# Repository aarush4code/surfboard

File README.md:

# surfboard

This is a devboard made with rp2040. It has 40 pins and 3 LEDs.

While making the devboard, or surfboard, I learned more about creating things in the kicad shematic, and how to route wires when their is a tight space. I also learned how to add labels to wire components together in the schematic.

## Images

## Bill of Materials
| Item                | Unit Price ($) | Link                                                                 | Quantity | Total ($) |
|---------------------|----------------|----------------------------------------------------------------------|----------|-----------|
| Capacitor 0.1uF     | 0.30           | [C52923](https://www.lcsc.com/product-detail/C52923.html?s_z=n_CL05A105KA5NQNC) | 11       | 3.30      |
| Capacitor 33pF      | 0.10           | [C1562](https://www.lcsc.com/product-detail/C1562.html?s_z=n_0402CG330J500NT)   | 2        | 0.20      |
| Capacitor 1uF       | 0.25           | [C42431804](https://www.lcsc.com/product-detail/C42431804.html)                 | 2        | 0.50      |
| Capacitor 10uF      | 0.29           | [C19702](https://www.lcsc.com/product-detail/C19702.html?s_z=n_CL10A106KP8NNNC) | 2        | 0.58      |
| Resistor 27Ω        | 0.60           | [C25100](https://www.lcsc.com/product-detail/C25100.html)                       | 2        | 1.20      |
| Resistor 1KΩ        | 0.06           | [C11702](https://www.lcsc.com/product-detail/C11702.html?s_z=n_0402WGF1001TCE)  | 2        | 0.12      |
| Resistor 5.1KΩ      | 0.05           | [C25905](https://www.lcsc.com/product-detail/C25905.html?s_z=n_0402WGF5101TCE)  | 2        | 0.10      |
| Resistor 10KΩ       | 0.06           | [C25744](https://www.lcsc.com/product-detail/C25744.html?s_z=n_0402WGF1002TCE)  | 1        | 0.06      |
| SK6812MINI LED      | 0.43           | [C5149201](https://www.lcsc.com/product-detail/C5149201.html)                   | 3        | 1.29      |
| 1x03 Pin Header     | 0.00           | [C42431804](https://www.lcsc.com/product-detail/C42431804.html)                 | 1        | 0.00      |
| 1x20 Pin Header     | 0.17           | [C42431804](https://www.lcsc.com/product-detail/C42431804.html)                 | 2        | 0.34      |
| 12 MHz Crystal      | 0.67           | [C9002](https://www.lcsc.com/product-detail/C9002.html?s_z=n_X322512MSB4SI)     | 1        | 0.67      |
| USB-C Receptacle    | 0.88           | [C165948](https://www.lcsc.com/product-detail/C165948.html?s_z=n_TYPE-C-31-M-12)| 1        | 0.88      |
| Flash Memory        | 0.95           | [C179171](https://www.lcsc.com/product-detail/C179171.html?s_z=n_Winbond%2520W25Q128JVSs)    | 1        | 1.60      |
| Voltage Regulator   | 0.33           | [C3054](https://www.lcsc.com/product-detail/C3054.html?s_z=n_IRFL9014TRPBF)     | 1        | 1.36      |
| Button              | 0.42           | [C2891841](https://www.lcsc.com/product-detail/C2891841.html)                     | 1        | 0.42      |
| RP2040              | 0.95           | [C2040](https://www.lcsc.com/product-detail/C2040.html?s_z=n_RP2040)            | 1        | 0.95      |
| PCBA                | 44.02          | [JLCPCB](https://jlcpcb.com)                                                    | 1        | 44.02     |
| **Total**           | --            | —                                                                                | —        | **57.89** |

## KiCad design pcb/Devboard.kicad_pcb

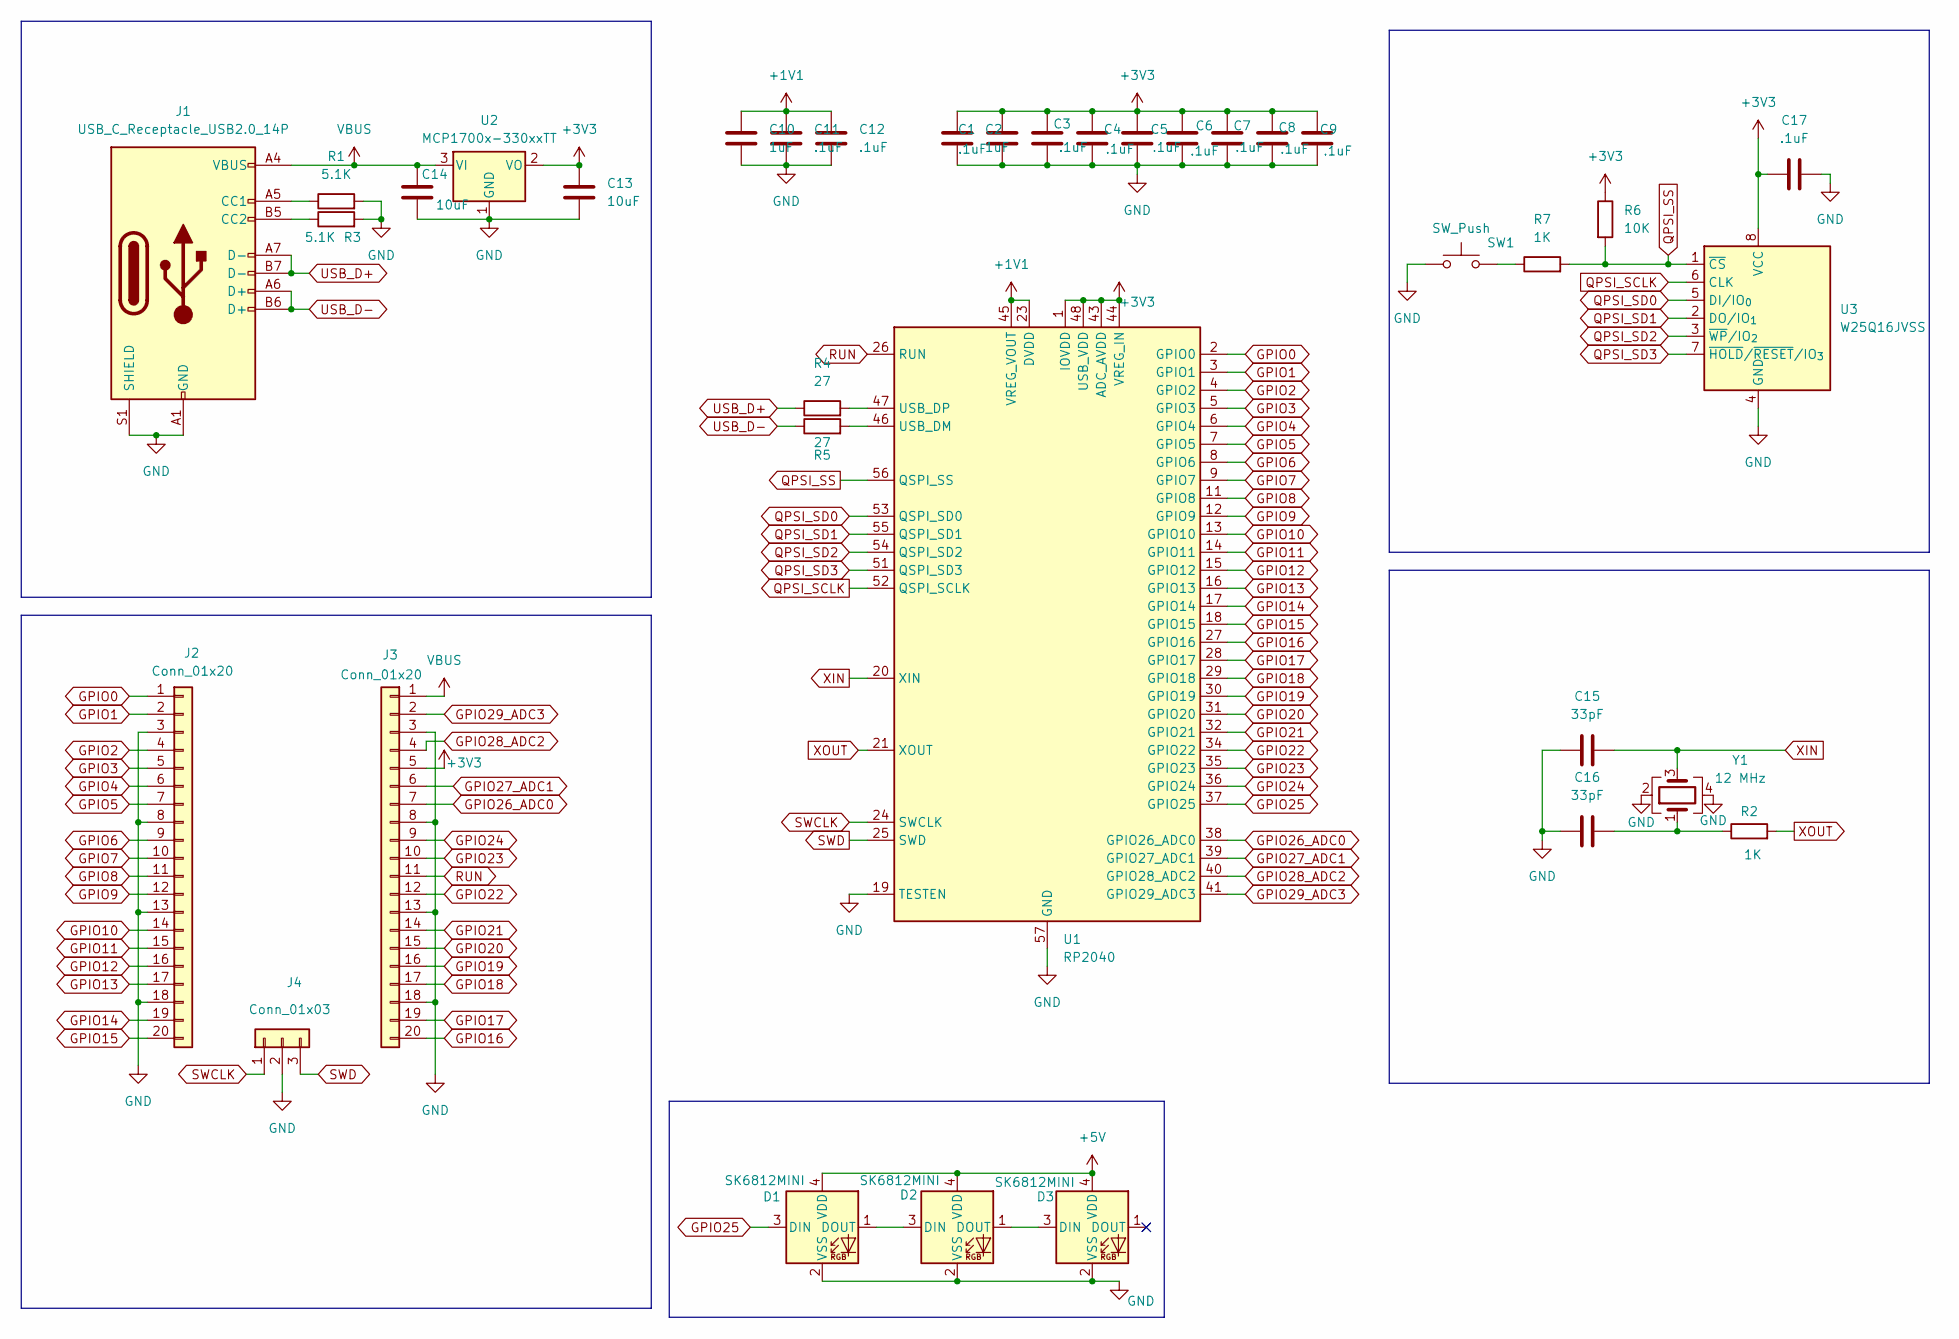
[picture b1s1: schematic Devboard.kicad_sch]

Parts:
C1, C3, C4, C5, C6, C7, C8, C9, C11, C12, C17: .1uF; C_0402_1005Metric
C2, C10: 1uF; C_0402_1005Metric
C13, C14: 10uF; C_0402_1005Metric
C15, C16: 33pF; C_0402_1005Metric
D1, D2, D3: SK6812MINI; LED_SK6812MINI_PLCC4_3.5x3.5mm_P1.75mm
J1: USB_C_Receptacle_USB2.0_14P; USB_C_Receptacle_HRO_TYPE-C-31-M-12
J2, J3: Conn_01x20; PinHeader_1x20_P2.54mm_Vertical
J4: Conn_01x03; PinHeader_1x03_P2.54mm_Vertical
R1, R3: 5.1K; R_0402_1005Metric
R2, R7: 1K; R_0402_1005Metric
R4, R5: 27; R_0402_1005Metric
R6: 10K; R_0402_1005Metric
SW1: SW_Push; SW_Push_SPST_NO_Alps_SKRK
U1: RP2040; QFN-56-1EP_7x7mm_P0.4mm_EP3.2x3.2mm
U2: MCP1700x-330xxTT; SOT-23
U3: W25Q16JVSS; Winbond_USON-8-1EP_3x2mm_P0.5mm_EP0.2x1.6mm
Y1: 12 MHz; Crystal_SMD_3225-4Pin_3.2x2.5mm

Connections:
+1V1: C10.1, C11.1, C12.1, U1.23 (DVDD), U1.45 (VREG_VOUT), U1.50 (DVDD)
+3V3: C1.1, C2.1, C3.1, C4.1, C5.1, C6.1, C7.1, C8.1, C9.1, C13.1, C17.1, J3.5, R6.1, U1.1 (IOVDD), U1.10 (IOVDD), U1.22 (IOVDD), U1.33 (IOVDD), U1.42 (IOVDD), U1.43 (ADC_AVDD), U1.44 (VREG_IN), U1.48 (USB_VDD), U1.49 (IOVDD), U2.2 (VO), U3.8 (VCC)
+5V: D1.4 (VDD), D2.4 (VDD), D3.4 (VDD)
GND: C1.2, C2.2, C3.2, C4.2, C5.2, C6.2, C7.2, C8.2, C9.2, C10.2, C11.2, C12.2, C13.2, C14.2, C15.1, C16.1, C17.2, D1.2 (VSS), D2.2 (VSS), D3.2 (VSS), J1.A1 (GND), J1.A12 (GND), J1.B1 (GND), J1.B12 (GND), J1.S1 (SHIELD), J2.3, J2.8, J2.13, J2.18, J3.3, J3.8, J3.13, J3.18, J4.2, R1.2, R3.2, SW1.1, U1.19 (TESTEN), U1.57 (GND), U2.1 (GND), U3.4 (GND), Y1.2, Y1.4
GPIO0: J2.1, U1.2 (GPIO0)
GPIO1: J2.2, U1.3 (GPIO1)
GPIO2: J2.4, U1.4 (GPIO2)
GPIO3: J2.5, U1.5 (GPIO3)
GPIO4: J2.6, U1.6 (GPIO4)
GPIO5: J2.7, U1.7 (GPIO5)
GPIO6: J2.9, U1.8 (GPIO6)
GPIO7: J2.10, U1.9 (GPIO7)
GPIO8: J2.11, U1.11 (GPIO8)
GPIO9: J2.12, U1.12 (GPIO9)
GPIO10: J2.14, U1.13 (GPIO10)
GPIO11: J2.15, U1.14 (GPIO11)
GPIO12: J2.16, U1.15 (GPIO12)
GPIO13: J2.17, U1.16 (GPIO13)
GPIO14: J2.19, U1.17 (GPIO14)
GPIO15: J2.20, U1.18 (GPIO15)
GPIO16: J3.20, U1.27 (GPIO16)
GPIO17: J3.19, U1.28 (GPIO17)
GPIO18: J3.17, U1.29 (GPIO18)
GPIO19: J3.16, U1.30 (GPIO19)
GPIO20: J3.15, U1.31 (GPIO20)
GPIO21: J3.14, U1.32 (GPIO21)
GPIO22: J3.12, U1.34 (GPIO22)
GPIO23: J3.10, U1.35 (GPIO23)
GPIO24: J3.9, U1.36 (GPIO24)
GPIO25: D1.3 (DIN), U1.37 (GPIO25)
GPIO26_ADC0: J3.7, U1.38 (GPIO26_ADC0)
GPIO27_ADC1: J3.6, U1.39 (GPIO27_ADC1)
GPIO28_ADC2: J3.4, U1.40 (GPIO28_ADC2)
GPIO29_ADC3: J3.2, U1.41 (GPIO29_ADC3)
unnamed: C16.2, R2.1, Y1.1
unnamed: D1.1 (DOUT), D2.3 (DIN)
unnamed: D2.1 (DOUT), D3.3 (DIN)
unnamed: J1.A5 (CC1), R1.1
unnamed: J1.B5 (CC2), R3.1
unnamed: R7.1, SW1.2
unnamed: R5.2, U1.46 (USB_DM)
unnamed: R4.2, U1.47 (USB_DP)
QPSI_SCLK: U1.52 (QSPI_SCLK), U3.6 (CLK)
QPSI_SD0: U1.53 (QSPI_SD0), U3.5 (DI/IO_{0})
QPSI_SD1: U1.55 (QSPI_SD1), U3.2 (DO/IO_{1})
QPSI_SD2: U1.54 (QSPI_SD2), U3.3 (~WP/IO_{2})
QPSI_SD3: U1.51 (QSPI_SD3), U3.7 (~HOLD/~RESET/IO_{3})
QPSI_SS: R6.2, R7.2, U1.56 (QSPI_SS), U3.1 (~CS)
RUN: J3.11, U1.26 (RUN)
SWCLK: J4.1, U1.24 (SWCLK)
SWD: J4.3, U1.25 (SWD)
USB_D+: J1.A7 (D-), J1.B7 (D-), R4.1
USB_D-: J1.A6 (D+), J1.B6 (D+), R5.1
VBUS: C14.1, J1.A4 (VBUS), J1.A9 (VBUS), J1.B4 (VBUS), J1.B9 (VBUS), J3.1, U2.3 (VI)
XIN: C15.2, U1.20 (XIN), Y1.3
XOUT: R2.2, U1.21 (XOUT)

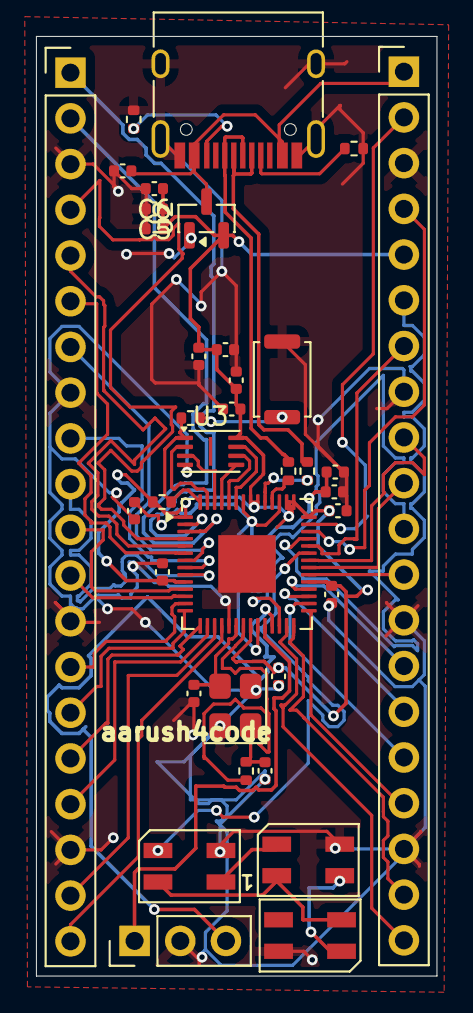
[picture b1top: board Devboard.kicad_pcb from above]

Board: 2 copper layers, 22.2 x 52.2 mm, 36 parts (0 on the bottom side), 56 nets.

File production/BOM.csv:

"Id";"Designator";"Footprint";"Quantity";"Designation";"Supplier and ref";
1;"C11,C12,C17,C8,C3,C9,C4,C1,C7,C6,C5";"C_0402_1005Metric";11;".1uF";;;
2;"C2,C10";"C_0402_1005Metric";2;"1uF";;;
3;"U3";"Winbond_USON-8-1EP_3x2mm_P0.5mm_EP0.2x1.6mm";1;"W25Q16JVSS";;;
4;"U2";"SOT-23";1;"MCP1700x-330xxTT";;;
5;"C16,C15";"C_0402_1005Metric";2;"33pF";;;
6;"J1";"USB_C_Receptacle_HRO_TYPE-C-31-M-12";1;"USB_C_Receptacle_USB2.0_14P";;;
7;"J3,J2";"PinHeader_1x20_P2.54mm_Vertical";2;"Conn_01x20";;;
8;"R2,R7";"R_0402_1005Metric";2;"1K";;;
9;"C14,C13";"C_0402_1005Metric";2;"10uF";;;
10;"D1,D2,D3";"LED_SK6812MINI_PLCC4_3.5x3.5mm_P1.75mm";3;"SK6812MINI";;;
11;"R5,R4";"R_0402_1005Metric";2;"27";;;
12;"J4";"PinHeader_1x03_P2.54mm_Vertical";1;"Conn_01x03";;;
13;"Y1";"Crystal_SMD_3225-4Pin_3.2x2.5mm";1;"12 MHz";;;
14;"R3,R1";"R_0402_1005Metric";2;"5.1K";;;
15;"SW1";"SW_Push_SPST_NO_Alps_SKRK";1;"SW_Push";;;
16;"U1";"QFN-56-1EP_7x7mm_P0.4mm_EP3.2x3.2mm";1;"RP2040";;;
17;"R6";"R_0402_1005Metric";1;"10K";;;

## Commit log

2025-12-04 Stop tracking ignored files
2025-12-04 added cad
2025-12-04 added bom
2025-12-04 added bom to readme
2025-12-04 finished firmware
2025-12-04 adding images to readme
2025-12-07 updated routing
2025-12-07 updated bom
